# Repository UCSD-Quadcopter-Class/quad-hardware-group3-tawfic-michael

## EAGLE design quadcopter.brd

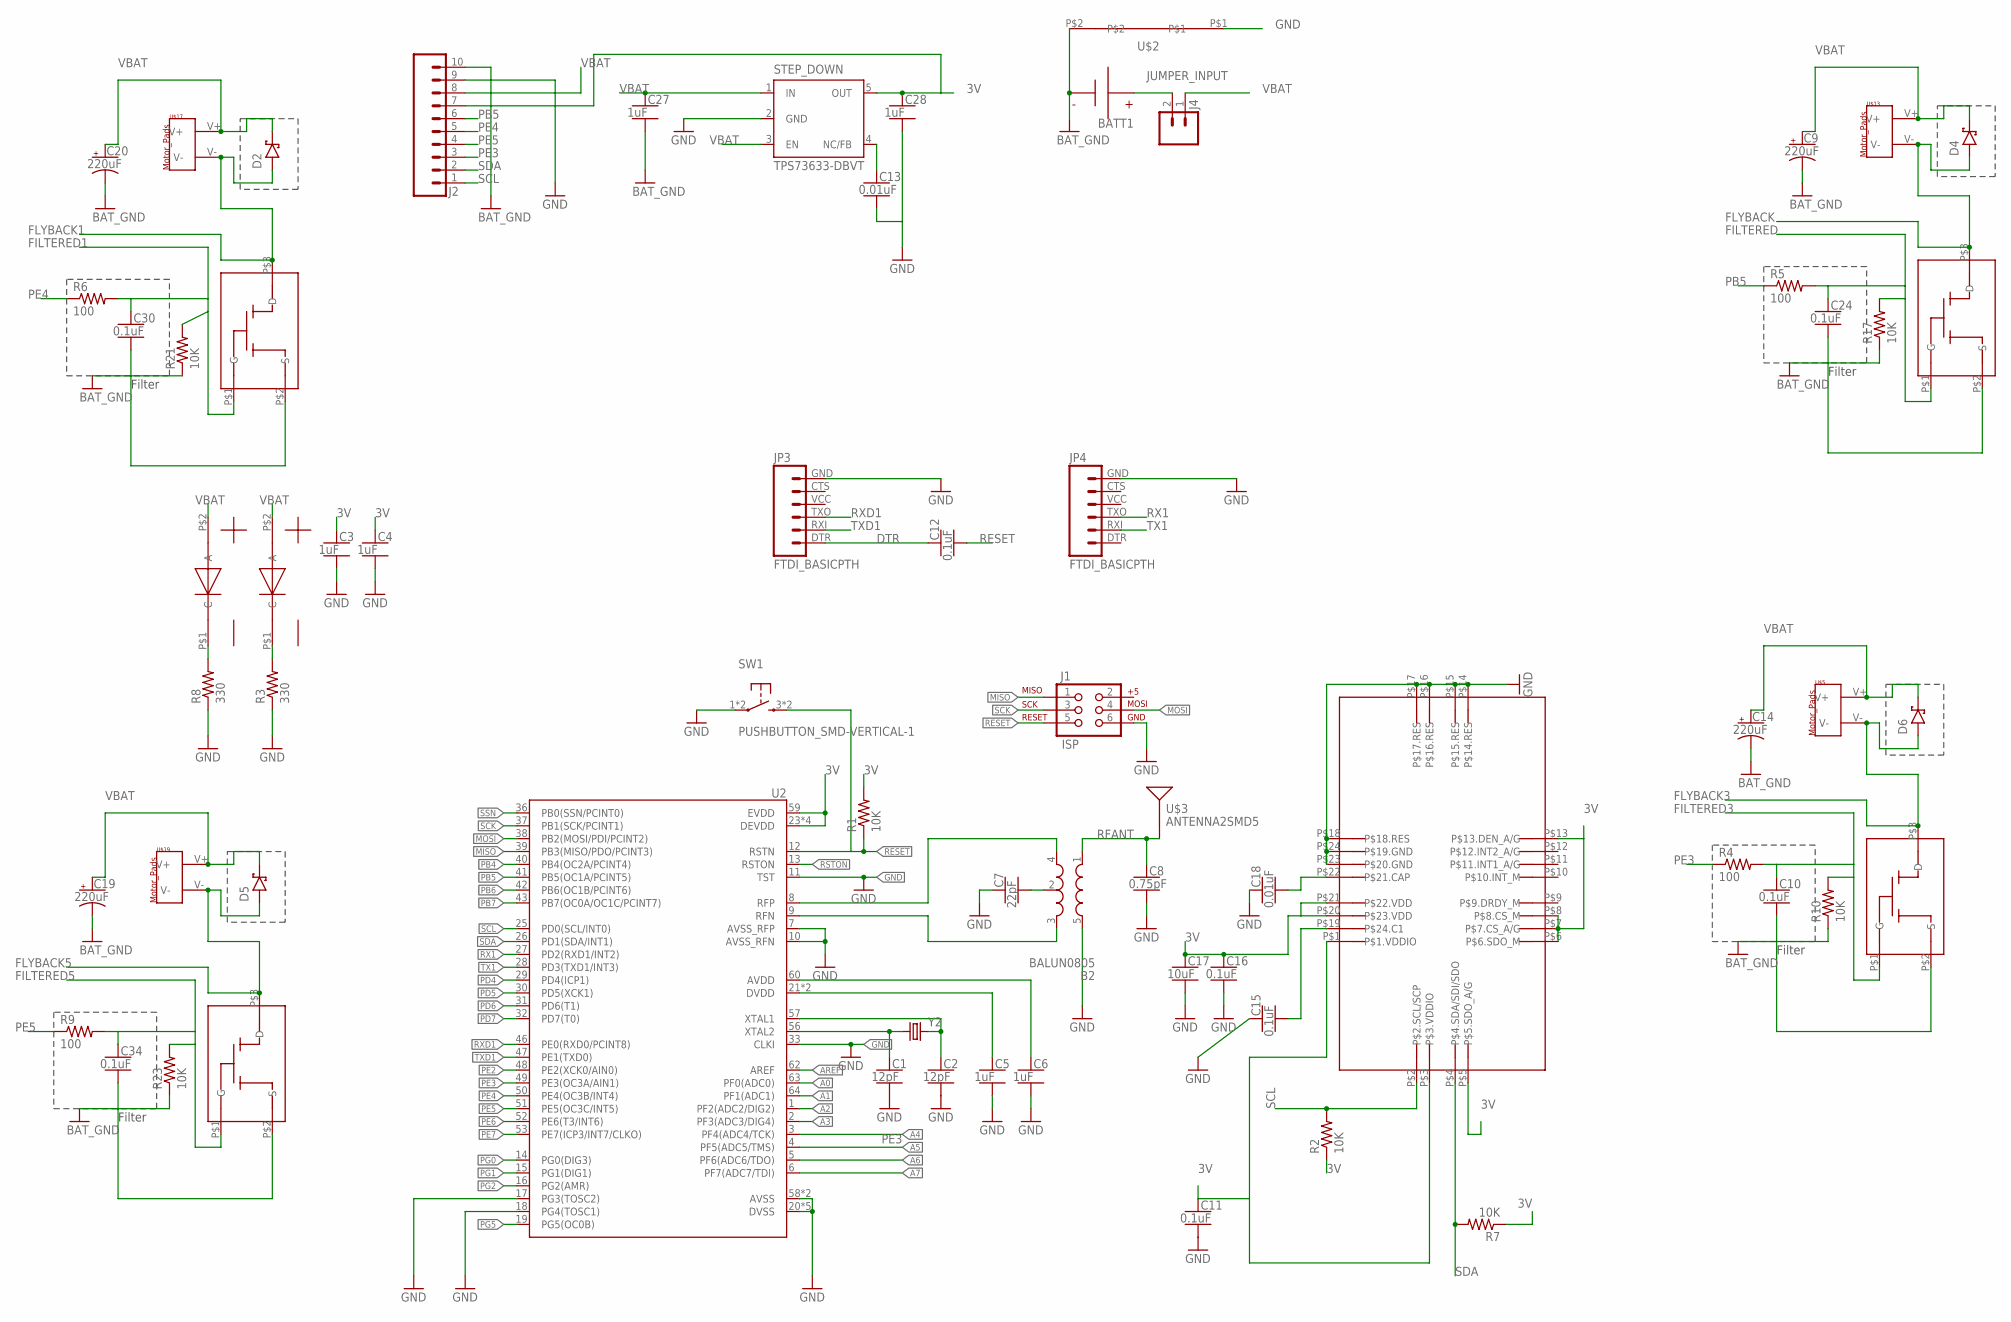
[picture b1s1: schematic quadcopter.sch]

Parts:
B2: BALUN0805; BALUN
BATT1: BATTERY-HUBSAN-W/HOLDER; BATTERY-W/HOLDER-380MAH-HUBSAN
C1, C2: 12pF; CAPC2012X140_HS
C3, C4, C5, C6, C27, C28: 1uF; CAPC2012X140_HS
C7: 22pF; CAPC2012X140_HS
C8: 0.75pF; CAPC2012X140_HS
C9, C14, C19, C20: 220uF; CAPMP7343X310_HS
C10, C11, C12, C15, C16, C24, C30, C34: 0.1uF; CAPC2012X140_HS
C13, C18: 0.01uF; CAPC2012X140_HS
C17: 10uF; CAPC2012X140_HS
D1, D3: LED-RED; RED_LED
D2, D4, D5, D6: DIODE-SCHOTTKY_SMD-SOD123; SOD3716X135_HS
J1: ISP; 2X3-NS
J2: SIP-10_TH-254X10-1; HDRV10W63P254_10X1_2540X254H838_HS
J4: MALE_HEADER_2POS-2X1-0.1IN; MALE_HEADER_2X1_0.1IN
JP3, JP4: FTDI_BASICPTH; FTDI_BASIC
R1, R2, R7, R10, R17, R21, R23: 10K; RESC2012X60_HS
R3, R8: 330; RESC2012X60_HS
R4, R5, R6, R9: 100; RESC2012X60_HS
STEP_DOWN: TPS73633-DBVT; SOT23-DBV
SW1: PUSHBUTTON_SMD-VERTICAL-1; TE_FSM8JSMA_HS
U2: ATMEGA128RFA1; QFN-64
U$1: LSM9DS1TR_IMU-9_AXIS; IMU
U$2: NET_BRIDGE
U$3: ANTENNA2SMD5; ANTENNA-CHIP5
U$5, U$13, U$17, U$19: MOTOR_PADS
U$7, U$16, U$18, U$20: MOSFET-N_CHANNEL; MOSFET
Y2: CRYSTAL5X3; CRYSTAL-SMD-5X3

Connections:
3V: C3.1, C4.1, C11.1, C16.1, C17.1, C28.1, J2.7, R1.2, R2.1, R7.1, STEP_DOWN.5 (OUT), U2.23 (DEVDD), U2.34 (DEVDD), U2.44 (DEVDD), U2.54 (DEVDD), U2.59 (EVDD), U$1.P$1 (P$1.VDDIO), U$1.P$3 (P$3.VDDIO), U$1.P$5 (P$5.SDO_A/G), U$1.P$6 (P$6.SDO_M), U$1.P$7 (P$7.CS_A/G), U$1.P$8 (P$8.CS_M), U$1.P$13 (P$13.DEN_A/G), U$1.P$20 (P$23.VDD), U$1.P$21 (P$22.VDD)
A0: U2.63 (PF0(ADC0))
A1: U2.64 (PF1(ADC1))
A2: U2.1 (PF2(ADC2/DIG2))
A3: U2.2 (PF3(ADC3/DIG4))
A4: U2.3 (PF4(ADC4/TCK))
A5: U2.4 (PF5(ADC5/TMS))
A6: U2.5 (PF6(ADC6/TDO))
A7: U2.6 (PF7(ADC7/TDI))
AREF: U2.62 (AREF)
AVDD: C6.1, U2.60 (AVDD)
BAT_GND: BATT1.- (N), C9.2 (-), C10.2, C14.2 (-), C19.2 (-), C20.2 (-), C24.2, C27.2, C30.2, C34.2, J2.10, R10.1, R17.1, R21.1, R23.1, U$2.P$2, U$7.P$2 (S), U$16.P$2 (S), U$18.P$2 (S), U$20.P$2 (S)
DTR: C12.1, JP3.DTR (1)
DVDD: C5.1, U2.21 (DVDD), U2.22 (DVDD)
FILTERED: C24.1, R5.2, R17.2, U$16.P$1 (G)
FILTERED1: C30.1, R6.2, R21.2, U$18.P$1 (G)
FILTERED3: C10.1, R4.2, R10.2, U$7.P$1 (G)
FILTERED5: C34.1, R9.2, R23.2, U$20.P$1 (G)
FLYBACK: D4.A, U$13.V-, U$16.P$3 (D)
FLYBACK1: D2.A, U$17.V-, U$18.P$3 (D)
FLYBACK3: D6.A, U$5.V-, U$7.P$3 (D)
FLYBACK5: D5.A, U$19.V-, U$20.P$3 (D)
GND: B2.5 (GND), C1.2, C2.2, C3.2, C4.2, C5.2, C6.2, C7.1, C8.2, C11.2, C13.2, C15.1, C16.2, C17.2, C18.1, C28.2, J1.6, J2.9, JP3.GND (6), JP4.GND (6), R3.1, R8.1, STEP_DOWN.2 (GND), SW1.1, SW1.2 (1), U2.7 (AVSS_RFP), U2.10 (AVSS_RFN), U2.11 (TST), U2.17 (PG3(TOSC2)), U2.18 (PG4(TOSC1)), U2.20 (DVSS), U2.24 (DVSS), U2.33 (CLKI), U2.35 (DVSS), U2.45 (DVSS), U2.55 (DVSS), U2.58 (AVSS), U2.61 (AVSS), U$1.P$14 (P$14.RES), U$1.P$15 (P$15.RES), U$1.P$16 (P$16.RES), U$1.P$17 (P$17.RES), U$1.P$18 (P$18.RES), U$1.P$23 (P$20.GND), U$1.P$24 (P$19.GND), U$2.P$1
JUMPER_INPUT: BATT1.+, J4.2
MISO: J1.1, U2.39 (PB3(MISO/PDO/PCINT3))
MOSI: J1.4, U2.38 (PB2(MOSI/PDI/PCINT2))
unnamed: C13.1, STEP_DOWN.4 (NC/FB)
unnamed: C2.1, U2.57 (XTAL1), Y2.3 (2)
unnamed: C1.1, U2.56 (XTAL2), Y2.1
unnamed: C18.2, U$1.P$22 (P$21.CAP)
unnamed: C15.2, U$1.P$19 (P$24.C1)
unnamed: B2.2 (GND), C7.2
unnamed: D3.P$1 (C), R8.2
unnamed: D1.P$1 (C), R3.2
PB4: U2.40 (PB4(OC2A/PCINT4))
PB5: J2.6, R5.1, U2.41 (PB5(OC1A/PCINT5))
PB6: U2.42 (PB6(OC1B/PCINT6))
PB7: U2.43 (PB7(OC0A/OC1C/PCINT7))
PD4: U2.29 (PD4(ICP1))
PD5: U2.30 (PD5(XCK1))
PD6: U2.31 (PD6(T1))
PD7: U2.32 (PD7(T0))
PE2: U2.48 (PE2(XCK0/AIN0))
PE3: J2.3, R4.1, U2.49 (PE3(OC3A/AIN1))
PE4: J2.5, R6.1, U2.50 (PE4(OC3B/INT4))
PE5: J2.4, R9.1, U2.51 (PE5(OC3C/INT5))
PE6: U2.52 (PE6(T3/INT6))
PE7: U2.53 (PE7(ICP3/INT7/CLKO))
PG0: U2.14 (PG0(DIG3))
PG1: U2.15 (PG1(DIG1))
PG2: U2.16 (PG2(AMR))
PG5: U2.19 (PG5(OC0B))
RESET: C12.2, J1.5, R1.1, SW1.3 (2), SW1.4 (2), U2.12 (RSTN)
RFANT: B2.1 (IN), C8.1, U$3.FEED
RFN: B2.3 (OUT2), U2.9 (RFN)
RFP: B2.4 (OUT1), U2.8 (RFP)
RSTON: U2.13 (RSTON)
RX1: JP4.TXO (3), U2.27 (PD2(RXD1/INT2))
RXD1: JP3.TXO (3), U2.46 (PE0(RXD0/PCINT8))
SCK: J1.3, U2.37 (PB1(SCK/PCINT1))
SCL: J2.1, R2.2, U2.25 (PD0(SCL/INT0)), U$1.P$2 (P$2.SCL/SCP)
SDA: J2.2, R7.2, U2.26 (PD1(SDA/INT1)), U$1.P$4 (P$4.SDA/SDI/SDO)
SSN: U2.36 (PB0(SSN/PCINT0))
TX1: JP4.RXI (2), U2.28 (PD3(TXD1/INT3))
TXD1: JP3.RXI (2), U2.47 (PE1(TXD0))
VBAT: C9.1 (+), C14.1 (+), C19.1 (+), C20.1 (+), C27.1, D1.P$2 (A), D2.C, D3.P$2 (A), D4.C, D5.C, D6.C, J2.8, J4.1, STEP_DOWN.1 (IN), STEP_DOWN.3 (EN), U$5.V+, U$13.V+, U$17.V+, U$19.V+

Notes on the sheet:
Filter

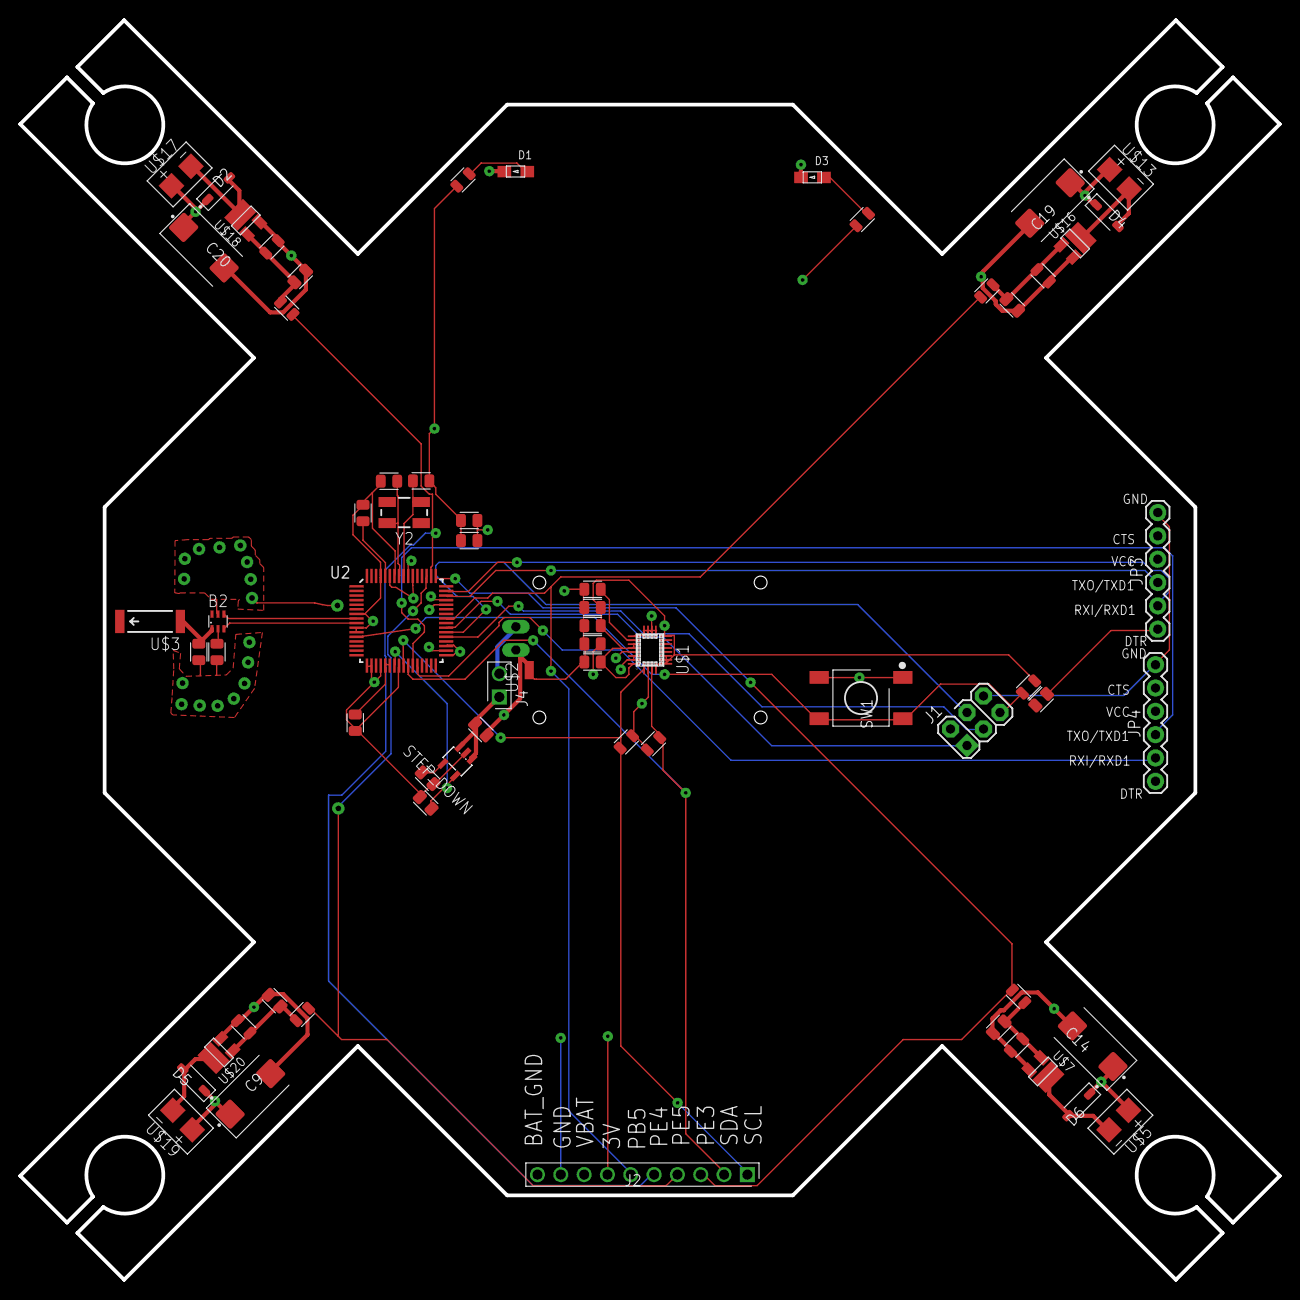
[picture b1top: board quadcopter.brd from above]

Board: 4 copper layers, 137.2 x 137.2 mm, 66 parts (1 on the bottom side), 41 nets.

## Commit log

2017-04-19 making sure connected to remote repository
2017-04-19 got rid of test file, added michael's quadparts library
2017-04-19 Worked through the microcontroller section, but didn't finish part 4. also think I need to replace their microcontroller
2017-04-20 added motor and header
2017-04-20 finished up everything
2017-04-20 almost forgot to include schematic
2017-04-27 instructior review of original schematic
2017-04-30 fixed stuff from design review
2017-04-30 almost forgot datasheet
2017-05-02 trying to work with pour, but can't move to internal layer. don't know why :(
2017-05-02 figured out pour, finished the gnd layer. need to continue from 3v and vbat pours
2017-05-02 Final Submsission
2017-05-02 Final Submssion
2017-05-02 fixed arm length
2017-05-03 There surely are a ton of mistakes, but I'm not sure what they are. I had to do a ton of routing by hand
2017-05-04 design reviews
2017-05-14 more schematic comments from swanson
2017-05-16 routed and everything
2017-05-16 worked on routing more, there are still lots of drc issues though
2017-05-16 lots of stop mask and tkeepout errors still, not sure what to do about them. haven't been able to look at dfm results yet
2017-05-16 Board comments from swanson
2017-05-16 autorouting works, things are good
2017-05-16 forgot cam zip files
2017-05-16 some old cam files deleted
2017-05-17 can't believe i forgot to push
2017-05-17 removed extra library files to clean up folder
2017-05-17 almost forgot newest board and schematic
2017-05-17 bigger mosfet pads, no vias leading to oscillator, cap 28 and 13 (?) go to gnd instead of bat_gnd, made antenna better
2017-05-17 changed most gnds on regulator to gnd instead of bat_gnd
2017-05-17 i think i forgot some airwires in last commit
2017-05-17 forgot cam files
2017-05-17 unzipped cam files
2017-05-18 moved net bridge and VREG closer to battery terminals
2017-05-18 fixed drc things for closer net bridge
2017-05-18 made vreg traces even shorter
2017-05-18 rotated board to fit in box
